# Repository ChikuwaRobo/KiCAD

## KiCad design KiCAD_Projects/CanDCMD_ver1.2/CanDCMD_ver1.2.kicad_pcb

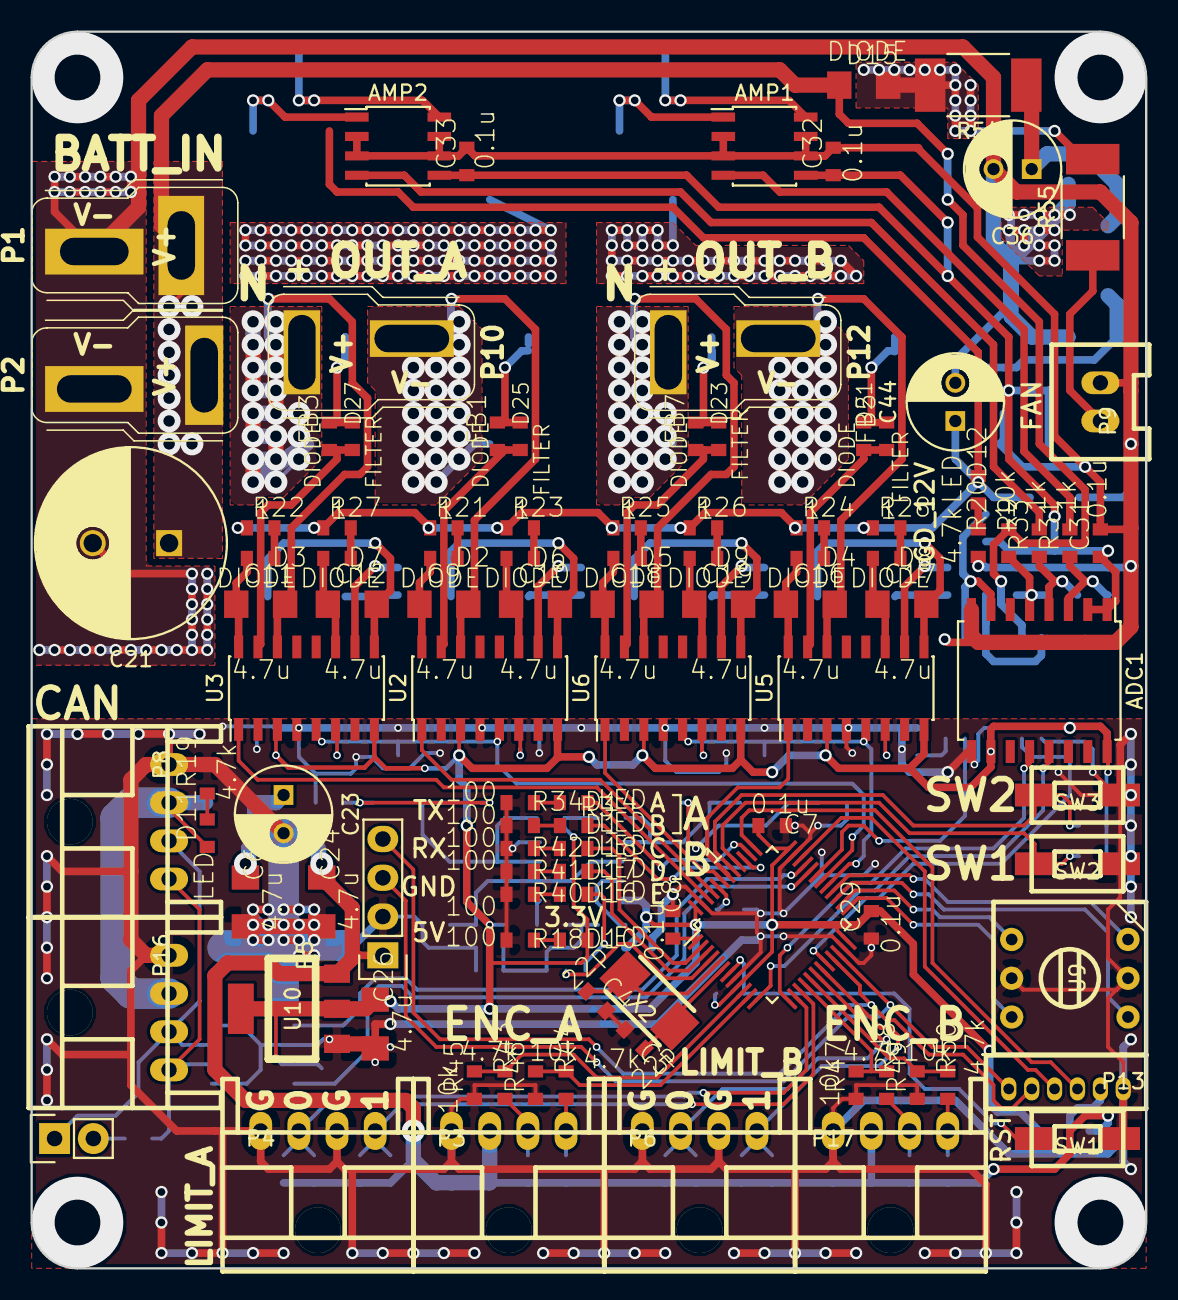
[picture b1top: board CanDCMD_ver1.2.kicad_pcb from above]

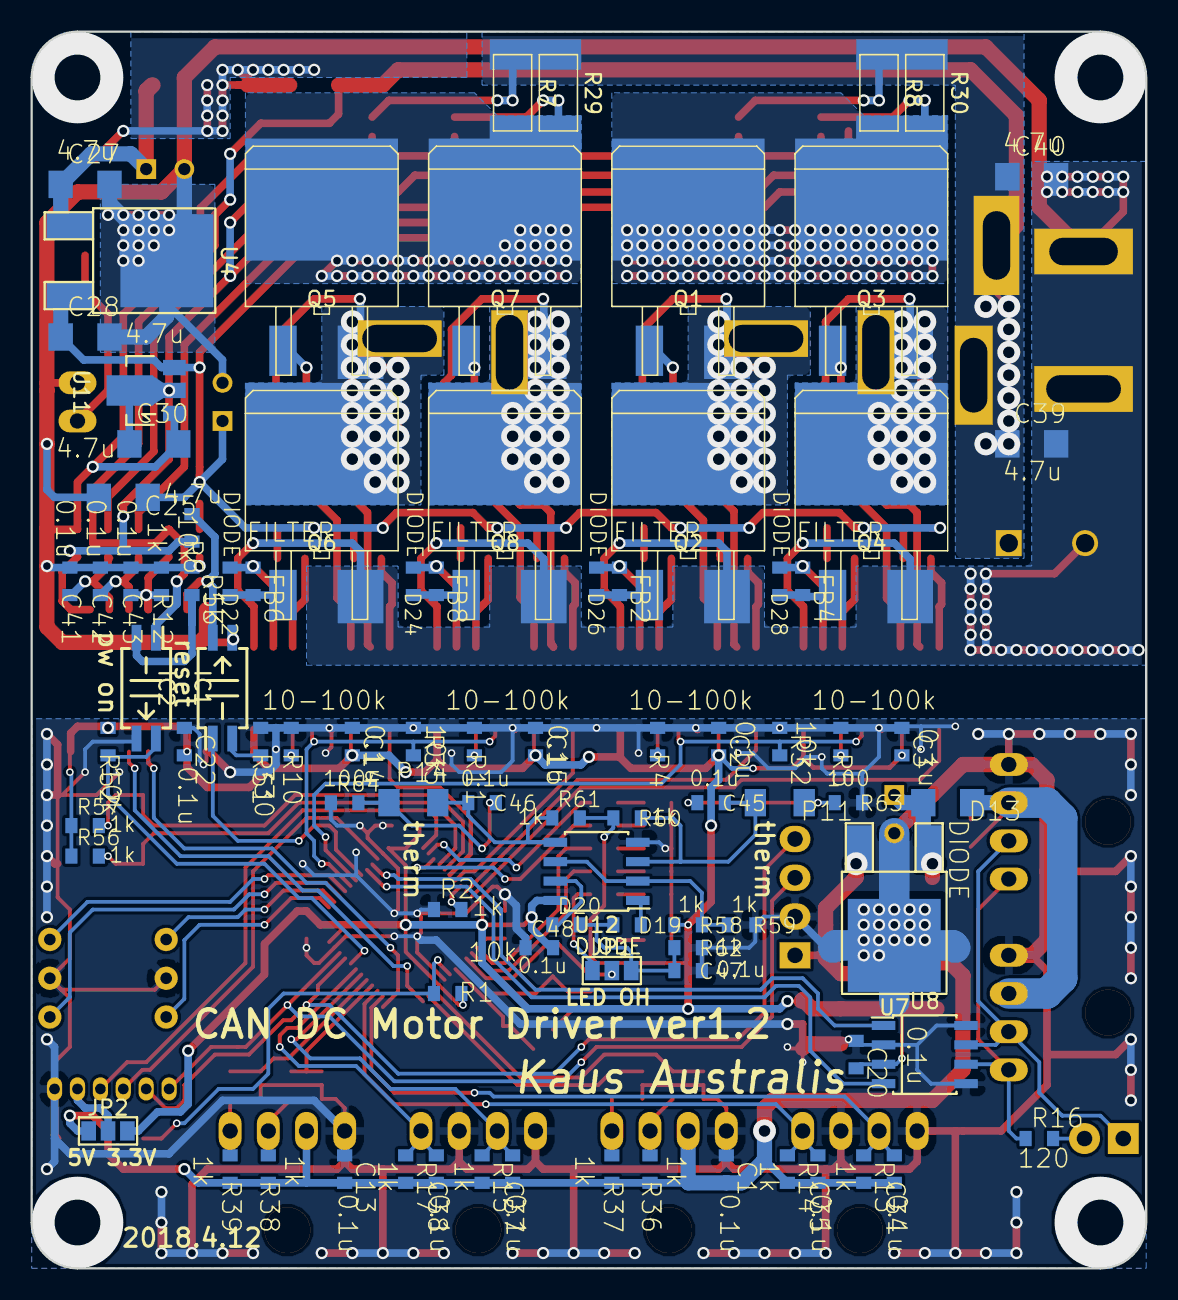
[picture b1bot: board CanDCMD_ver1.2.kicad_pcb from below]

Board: 2 copper layers, 73.0 x 81.0 mm, 195 parts (90 on the bottom side), 126 nets.

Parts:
ADC1: Si8900; SOIC-16_7.5x10.3mm_Pitch1.27mm
AMP1, AMP2: TSC103; SOIC-8_3.9x4.9mm_Pitch1.27mm
C1, C2, C3, C7, C8, C13, C14, C15, C20, C22, C29, C31, C32, C33, C34, C35, C37, C38, C41, C42, C43, C45, C46, C47, C48: 0.1u; C1608_WP
C4, C5: 22p; C1608_WP
C6, C9, C10, C11, C12, C16, C17, C18, C19, C24, C25, C26, C27, C28, C30, C39, C40: 4.7u; C3216
C21: 470u; C_Radial_D12.5_L25_P5
C23, C36, C44: 100u; C_Radial_D6.3_L11.2_P2.5
D1, D10, D11, D12, D14, D16, D17, D18: LED; C1608_WP
D2, D3, D4, D5, D6, D7, D8, D9, D19, D20, D21, D22, D23, D24, D25, D26, D27, D28: DIODE; C1608_WP
D13, D15: DIODE; C3216
FB1, FB2, FB3, FB4, FB5, FB6, FB7, FB8: FILTER; C1608_WP
IC1, IC2: TLP291; SOIJ-4_5.3x5.3mm_Pitch1.27mm
JP1, JP2: JUMPER3; GS3
P1: CONN_01X02; DEANS_T_M
P2: CONN_01X02; DEANS_T_F
P3, P4, P6, P8, P16, P17: CONN_01X04; XA_4LC
P5: CONN_01X04; Socket_Strip_Straight_1x04
P7: CONN_01X02; Pin_Header_Straight_1x02
P9: CONN_01X02; XA_2T
P10, P12: CONN_01X02; DEANS_T_F_minPad
P11, P14: CONN_01X02; C3216_S
P13: CONN_01X06; ZH_6T
Q1, Q2, Q3, Q4, Q5, Q6, Q7, Q8: MOSFET_N; D2-PAK_compact
R1, R9, R32, R35, R45, R46, R47, R49, R52, R53: 10k; C1608_WP
R2, R6, R12, R13, R14, R15, R17, R31, R33, R36, R37, R38, R39, R56, R57, R58, R59, R60, R61, R62: 1k; C1608_WP
R3, R18, R34, R40, R41, R42, R63, R64: 100; C1608_WP
R4, R5, R10, R11: 10-100k; C1608_WP
R7, R8, R29, R30: 1m; R5025
R16: 120; C1608_WP
R19, R20, R43, R44, R48, R50: 4.7k; C1608_WP
R21, R22, R23, R24, R25, R26, R27, R28: 1; C1608_WP
R51: 330; C1608_WP
R54, R55: 5; R_2812
SW1, SW2, SW3: SW_PUSH; RP_SMD_Button
U1: STM32F103_48; LQFP-48_7x7mm_Pitch0.5mm
U2, U3, U5, U6: SI8234; SOIC-16_3.9x9.9mm_Pitch1.27mm
U4: LM7812; TO-252-2Lead_regu
U7: 7805; TO-252-2Lead_regu
U8: MAX3051; SOIC-8_3.9x4.9mm_Pitch1.27mm
U9: SW_ROTARY_16; rotary_0F
U10: NCP1117ST33T3G; SOT-223_reg
U11: LM1084IS-3.3/NOPB; SOT89-3_Housing
U12: LM358N; SOIC-8_3.9x4.9mm_Pitch1.27mm
X2: CRYSTAL; ABM3_2pads

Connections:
+3.3V: ADC1.10, ADC1.16, C2.2, C3.2, C7.2, C8.2, C14.2, C15.2, C20.2, C22.2, C26.1, C29.2, C48.2, D10.1, JP2.3, R1.1, R52.2, R56.1, R57.1, R58.2, R60.2, R61.2, U1.1, U1.9, U1.24, U1.36, U1.48, U2.3, U2.8, U3.3, U3.8, U5.3, U5.8, U6.3, U6.8, U8.3, U10.2, U12.8
+5V: C1.2, C13.2, C24.1, C34.1, C35.1, C37.1, C38.1, JP2.1, P3.2, P5.1, P17.2, R13.2, R14.2, R15.2, R17.2, R36.1, R37.1, R38.1, R39.1, U7.VO, U10.3
+12V: D11.1, D13.1, P8.2, P16.2
+BATT: AMP1.8, AMP2.8, C21.1, C39.1, C40.1, D15.1, IC1.1, P1.1, P2.1, R7.1, R8.1, R9.1, R29.1, R30.1
/ADC_RX: ADC1.12, U1.13
/ADC_TX: ADC1.13, U1.12
/ADC_~RST: IC2.1, U1.31
/BOOT0: R2.2, U1.44
/Batt+: ADC1.5, C43.1, R9.2, R12.1
/CANH: P7.1, P8.3, P16.3, U8.7
/CANL: P8.4, P16.4, R16.1, U8.6
/CAN_RX: U1.32, U8.4
/CAN_TX: U1.33, U8.1
/CurrentA: AMP2.4, R33.2
/CurrentB: AMP1.4, R31.2
/ENC_Aa: P3.3, R36.2, R43.2
/ENC_Ab: P3.4, R37.2, R44.2
/ENC_Ba: P17.3, R38.2, R48.2
/ENC_Bb: P17.4, R39.2, R50.2
/GD_12V: C25.1, C28.1, C44.1, D12.1, R21.1, R22.1, R23.1, R24.1, R25.1, R26.1, R27.1, R28.1, U4.VO, U11.3
/LED_A: D14.1, U1.38
/LED_B: D1.1, U1.39
/LED_C: D18.1, U1.2
/LED_D: D17.1, U1.3
/LED_E: D16.1, JP1.1
/LIMIT_A0: C34.2, P4.2, R13.1, U1.14
/LIMIT_A1: C35.2, P4.4, R14.1, U1.15
/LIMIT_B0: C37.2, P6.2, R15.1, U1.18
/LIMIT_B1: C38.2, P6.4, R17.1, U1.19
/MOTORA_BATT: AMP2.1, Q1.D, Q3.D, R8.2, R30.2
/MOTORA_EN: R32.2, U1.30, U2.5, U3.5
/MOTORB_BATT: AMP1.1, Q5.D, Q7.D, R7.2, R29.2
/MOTORB_EN: R35.2, U1.29, U5.5, U6.5
/NRST: R1.2, SW1.2, U1.7
/OH: C47.2, D19.2, D20.2, JP1.3, R62.2
/OH_LEDE: JP1.2, U1.4
/OH_SH: R58.1, R59.2, U12.2, U12.6
/OSC_IN: C4.1, U1.5, X2.1
/OSC_OUT: C5.1, U1.6, X2.2
/OUT_A: C9.2, P10.2, Q1.S, Q2.D, U2.14
/OUT_AN: C11.2, P10.1, Q3.S, Q4.D, U3.14
/OUT_B: C16.2, P12.2, Q5.S, Q6.D, U5.14
/OUT_BN: C18.2, P12.1, Q7.S, Q8.D, U6.14
/PWM_A: U1.45, U2.1
/PWM_AN: U1.46, U3.1
/PWM_B: U1.42, U5.1
/PWM_BN: U1.43, U6.1
/PW_3.3V: ADC1.1, ADC1.2, AMP1.5, AMP2.5, C30.1, C31.1, C32.1, C33.1, R6.1, U11.2
/PowerOn: IC1.4, R52.1, U1.20
/SEL_1: U1.28, U9.3
/SEL_2: U1.27, U9.1
/SEL_4: U1.26, U9.4
/SEL_8: U1.25, U9.6
/SW1: R56.2, SW2.2, U1.40
/SW2: R57.2, SW3.2, U1.41
/SWCLK: P13.3, U1.37
/SWDIO: P13.4, U1.34
/Theam_A: C45.1, P11.2, R60.1, U12.3
/Theam_B: C46.2, P14.2, R61.1, U12.5
/USART_RX: P5.3, P13.6, U1.22
/USART_TX: P5.4, P13.5, U1.21
GND: ADC1.9, C1.1, C2.1, C3.1, C4.2, C5.2, C6.2, C7.1, C8.1, C13.1, C14.1, C15.1, C20.1, C22.1, C23.2, C24.2, C26.2, C29.1, C47.1, C48.1, IC1.3, P3.1, P4.1, P4.3, P5.2, P6.1, P6.3, P8.1, P13.1, P16.1, P17.1, R2.1, R3.2, R4.2, R5.2, R10.2, R11.2, R18.2, R19.2, R32.1, R34.2, R35.1, R40.2, R41.2, R42.2, R45.1, R46.1, R47.1, R49.1, R51.2, R59.1, R62.1, R63.1, R64.1, SW1.1, SW2.1, SW3.1, U1.8, U1.23, U1.35, U1.47, U2.4, U3.4, U5.4, U6.4, U7.GND, U8.2, U8.5, U8.8, U9.2, U9.5, U10.1, U12.4
GNDPWR: ADC1.8, AMP1.2, AMP1.3, AMP1.6, AMP1.7, AMP2.2, AMP2.3, AMP2.6, AMP2.7, C10.2, C12.2, C17.2, C19.2, C21.2, C25.2, C27.2, C28.2, C30.2, C31.2, C32.2, C33.2, C36.2, C39.2, C40.2, C41.2, C42.2, C43.2, C44.2, IC2.3, P1.2, P2.2, P9.1, Q2.S, Q4.S, Q6.S, Q8.S, R12.2, R20.2, R53.1, U2.9, U3.9, U4.GND, U5.9, U6.9, U11.1
unnamed: ADC1.3, C41.1, R31.1
unnamed: ADC1.4, C42.1, R33.1
unnamed: ADC1.7, IC2.4, R6.2
unnamed: C9.1, D2.2, U2.16
unnamed: C10.1, D6.2, U2.11
unnamed: C11.1, D3.2, U3.16
unnamed: C12.1, D7.2, U3.11
unnamed: C16.1, D4.2, U5.16
unnamed: C17.1, D8.2, U5.11
unnamed: C18.1, D5.2, U6.16
unnamed: C19.1, D9.2, U6.11
unnamed: C6.1, C23.1, D13.2, U7.VI
unnamed: C27.1, C36.1, R54.1, U4.VI
unnamed: C45.2, P11.1, R63.2
unnamed: C46.1, P14.1, R64.2
unnamed: D1.2, R3.1
unnamed: D2.1, R21.2
unnamed: D3.1, R22.2
unnamed: D4.1, R24.2
unnamed: D5.1, R25.2
unnamed: D6.1, R23.2
unnamed: D7.1, R27.2
unnamed: D8.1, R28.2
unnamed: D9.1, R26.2
unnamed: D10.2, R18.1
unnamed: D11.2, R19.1
unnamed: D12.2, R20.1
unnamed: D14.2, R34.1
unnamed: D15.2, R54.2, R55.2
unnamed: D16.2, R40.1
unnamed: D17.2, R41.1
unnamed: D18.2, R42.1
unnamed: D19.1, U12.1
unnamed: D20.1, U12.7
unnamed: D21.1, FB5.2, Q5.G
unnamed: D21.2, FB5.1, U5.15
unnamed: D22.1, FB6.2, Q6.G
unnamed: D22.2, FB6.1, U5.10
unnamed: D23.1, FB7.2, Q7.G
unnamed: D23.2, FB7.1, U6.15
unnamed: D24.1, FB8.2, Q8.G
unnamed: D24.2, FB8.1, U6.10
unnamed: D25.1, FB1.2, Q1.G
unnamed: D25.2, FB1.1, U2.15
unnamed: D26.1, FB2.2, Q2.G
unnamed: D26.2, FB2.1, U2.10
unnamed: D27.1, FB3.2, Q3.G
unnamed: D27.2, FB3.1, U3.15
unnamed: D28.1, FB4.2, Q4.G
unnamed: D28.2, FB4.1, U3.10
unnamed: IC1.2, R53.2
unnamed: IC2.2, R51.1
unnamed: JP2.2, P13.2
unnamed: P7.2, R16.2
unnamed: P9.2, R55.1
unnamed: R4.1, U2.6
unnamed: R5.1, U3.6
unnamed: R10.1, U5.6
unnamed: R11.1, U6.6
unnamed: R43.1, R45.2, U1.10
unnamed: R44.1, R46.2, U1.11
unnamed: R47.2, R48.1, U1.16
unnamed: R49.2, R50.1, U1.17

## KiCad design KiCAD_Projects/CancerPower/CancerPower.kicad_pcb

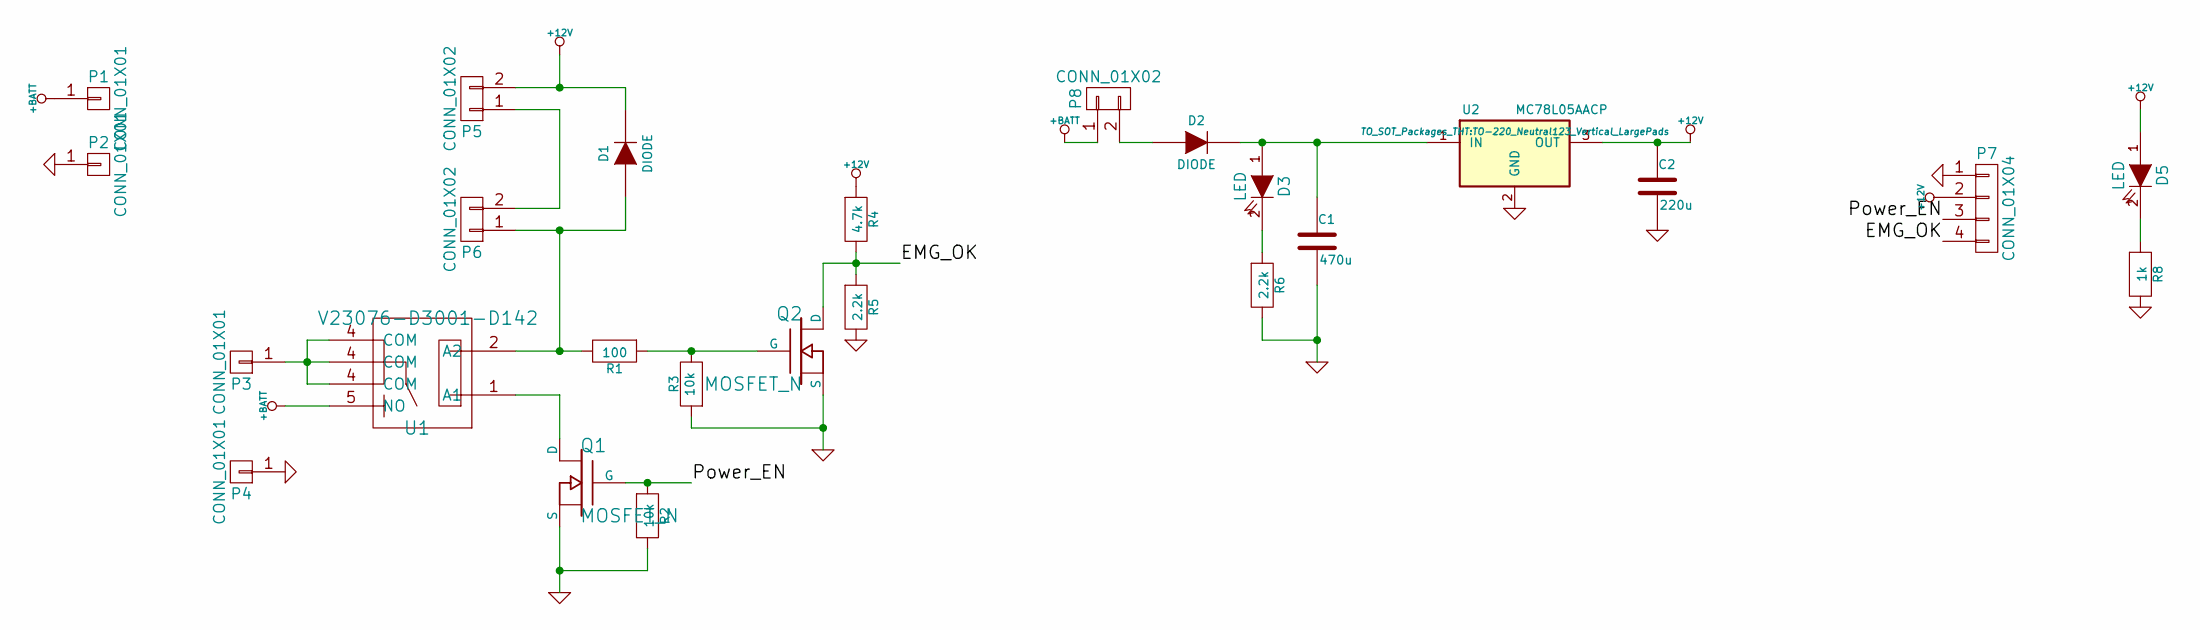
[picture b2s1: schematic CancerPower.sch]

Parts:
C1: 470u; C_Radial_D8_L11.5_P3.5
C2: 220u; C_Radial_D6.3_L11.2_P2.5
D1: DIODE; SMA_Handsoldering
D2: DIODE; Diode_DO-41_SOD81_Horizontal_RM10
D3, D5: LED; LED-3MM
P1, P2, P3, P4: CONN_01X01; 1pin
P5, P6, P8: CONN_01X02; XA_2LC
P7: CONN_01X04; XA_4LC
Q1, Q2: MOSFET_N; SOT-23_Handsoldering
R1: 100; 0204_2f5
R2, R3: 10k; C1608_WP
R4: 4.7k; C1608_WP
R5, R6: 2.2k; C1608_WP
R8: 1k; C1608_WP
U1: V23076-D3001-D142; V23076-A3001-D142
U2: MC78L05AACP; TO-220_Neutral123_Vertical_LargePads

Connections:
+12V: C2.1, D1.1 (K), D5.1 (A), P5.2, P7.2, R4.1, U2.3 (OUT); also elsewhere on the board
+BATT: P1.1, P8.1, U1.5 (NO)
/EMG_OK: P7.4, Q2.D, R4.2, R5.1
/Power_EN: P7.3, Q1.G, R2.1
GND: C1.2, C2.2, P2.1, P4.1, P7.1, Q1.S, Q2.S, R2.2, R3.1, R5.2, R6.2, R8.2, U2.2 (GND); also elsewhere on the board
unnamed 5: C1.1, D2.1 (K), D3.1 (A), U2.1 (IN); also elsewhere on the board
unnamed: D1.2 (A), P6.1, R1.2, U1.2 (A2)
unnamed: D2.2 (A), P8.2
unnamed: D3.2 (K), R6.1
unnamed: D5.2 (K), R8.1
unnamed: P3.1, U1.4 (COM)
unnamed: P5.1, P6.2
unnamed: Q1.D, U1.1 (A1)
unnamed: Q2.G, R1.1, R3.2

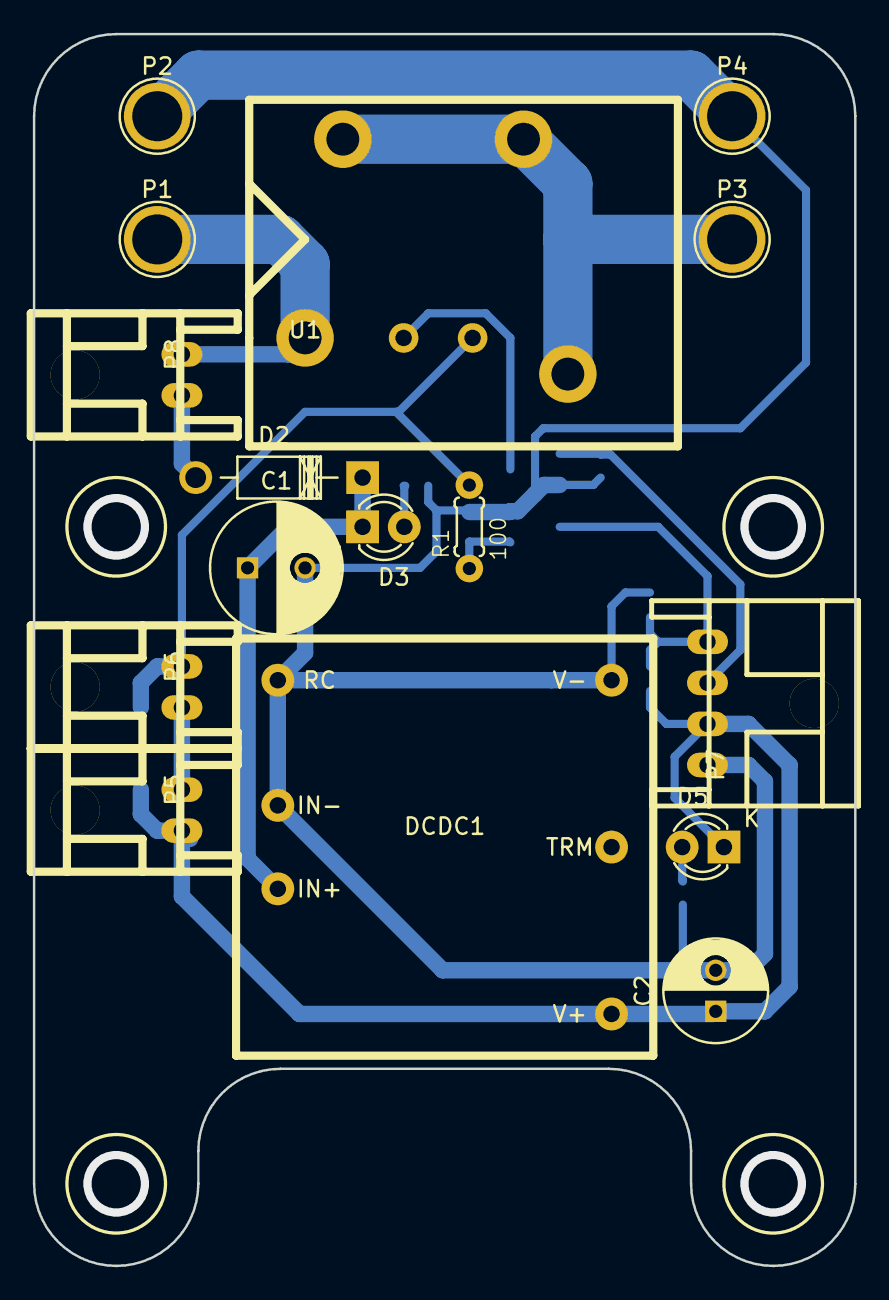
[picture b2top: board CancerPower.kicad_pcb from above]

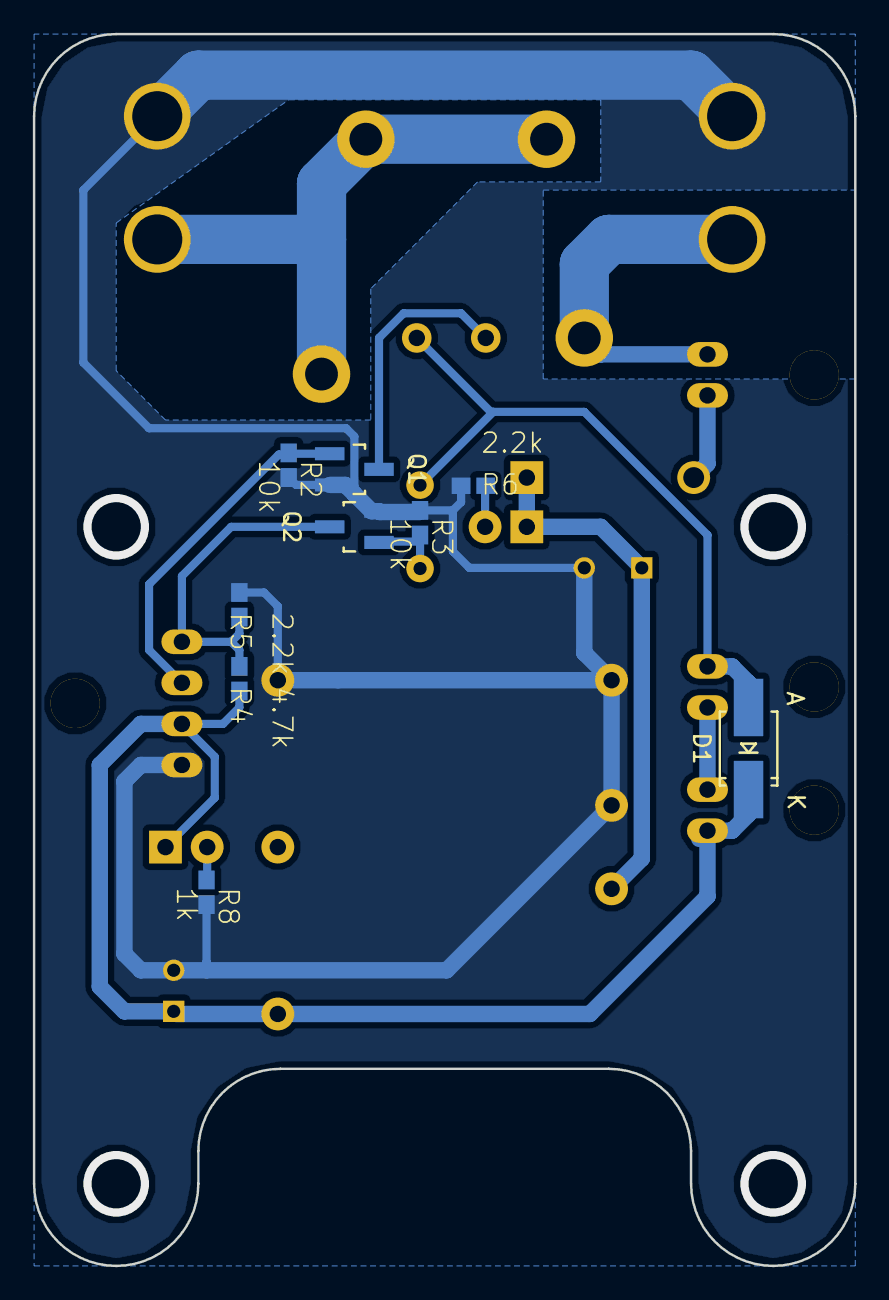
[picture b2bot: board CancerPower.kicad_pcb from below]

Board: 2 copper layers, 50.0 x 75.0 mm, 25 parts (9 on the bottom side), 14 nets.

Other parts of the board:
DCDC1: MGS15

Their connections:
+12V: DCDC1.1; also elsewhere on the board
GND: DCDC1.3, DCDC1.4, DCDC1.5; also elsewhere on the board
unnamed 5: DCDC1.6; also elsewhere on the board
